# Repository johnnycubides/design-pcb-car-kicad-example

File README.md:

# design-pcb-car-kicad-example

Example of design a pcb in kicad for car project with esp32

Regards

Johnny Cubides

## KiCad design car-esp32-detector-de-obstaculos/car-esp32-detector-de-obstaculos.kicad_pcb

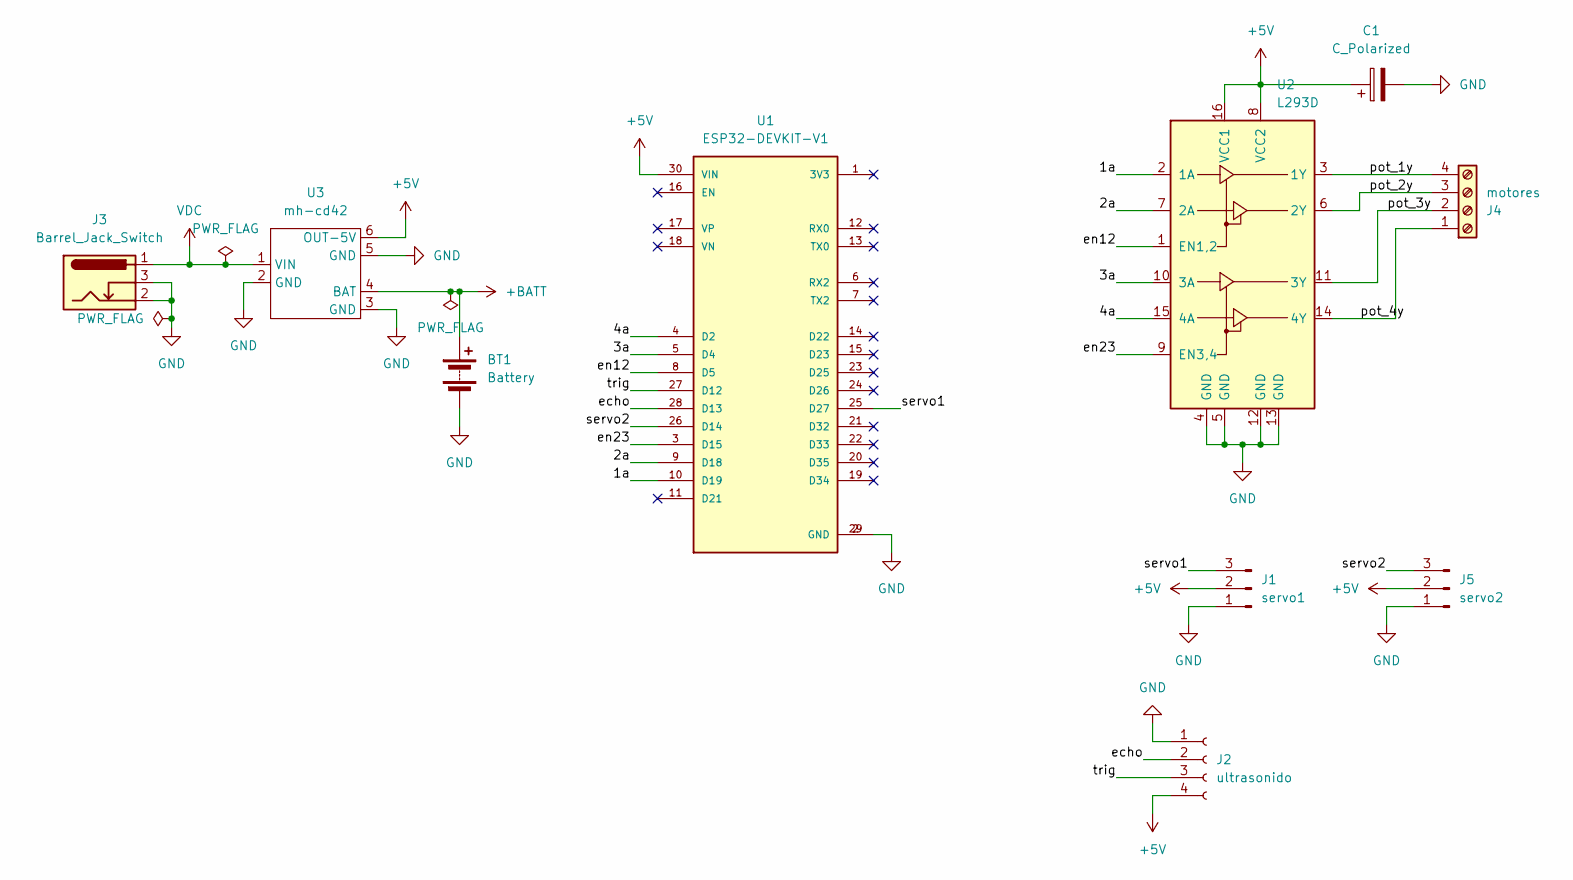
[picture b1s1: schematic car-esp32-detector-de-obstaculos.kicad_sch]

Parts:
BT1: Battery; BatteryHolder_Keystone_1042_1x18650
C1: C_Polarized; CP_Radial_D5.0mm_P2.00mm
J1: servo1; PinHeader_1x03_P2.54mm_Vertical
J2: ultrasonido; PinSocket_1x04_P2.54mm_Vertical
J3: Barrel_Jack_Switch; BarrelJack_Horizontal
J4: motores; TerminalBlock_bornier-4_P5.08mm
J5: servo2; PinHeader_1x03_P2.54mm_Vertical
U1: ESP32-DEVKIT-V1; MODULE_ESP32_DEVKIT_V1; PARTREV N/A
U2: L293D; DIP-16_W7.62mm
U3: mh-cd42

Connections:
+5V: C1.1, J1.2, J2.4, J5.2, U1.30 (VIN), U2.8 (VCC2), U2.16 (VCC1), U3.6 (OUT-5V)
+BATT: BT1.1 (+), U3.4 (BAT)
/1a: U1.10 (D19), U2.2 (1A)
/2a: U1.9 (D18), U2.7 (2A)
/3a: U1.5 (D4), U2.10 (3A)
/4a: U1.4 (D2), U2.15 (4A)
/echo: J2.2, U1.28 (D13)
/en12: U1.8 (D5), U2.1 (EN1,2)
/en23: U1.3 (D15), U2.9 (EN3,4)
/pot_1y: J4.4, U2.3 (1Y)
/pot_2y: J4.3, U2.6 (2Y)
/pot_3y: J4.2, U2.11 (3Y)
/pot_4y: J4.1, U2.14 (4Y)
/servo1: J1.3, U1.25 (D27)
/servo2: J5.3, U1.26 (D14)
/trig: J2.3, U1.27 (D12)
GND: BT1.2 (-), C1.2, J1.1, J2.1, J3.2, J3.3, J5.1, U1.2 (GND), U1.29 (GND), U2.4 (GND), U2.5 (GND), U2.12 (GND), U2.13 (GND), U3.2 (GND), U3.3 (GND), U3.5 (GND)
VDC: J3.1, U3.1 (VIN)

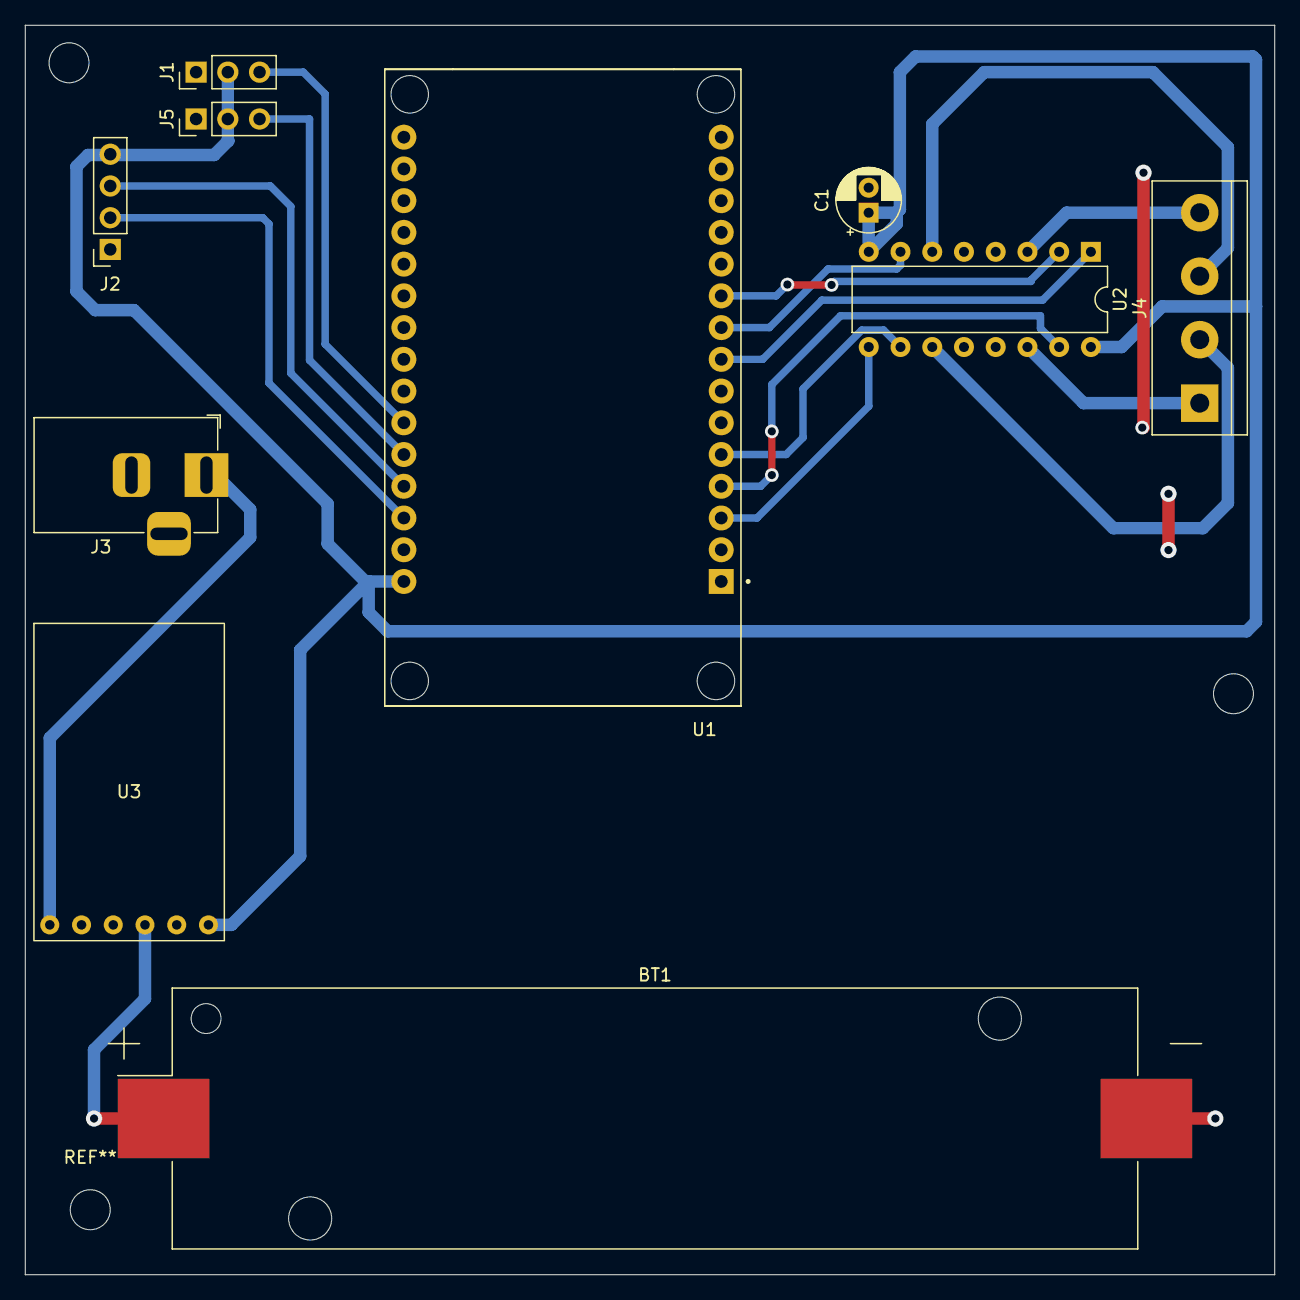
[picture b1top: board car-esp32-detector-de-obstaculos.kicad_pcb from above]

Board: 2 copper layers, 100.0 x 100.0 mm, 10 parts (0 on the bottom side), 18 nets.

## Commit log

2024-08-21 update all
2024-08-26 update docs
